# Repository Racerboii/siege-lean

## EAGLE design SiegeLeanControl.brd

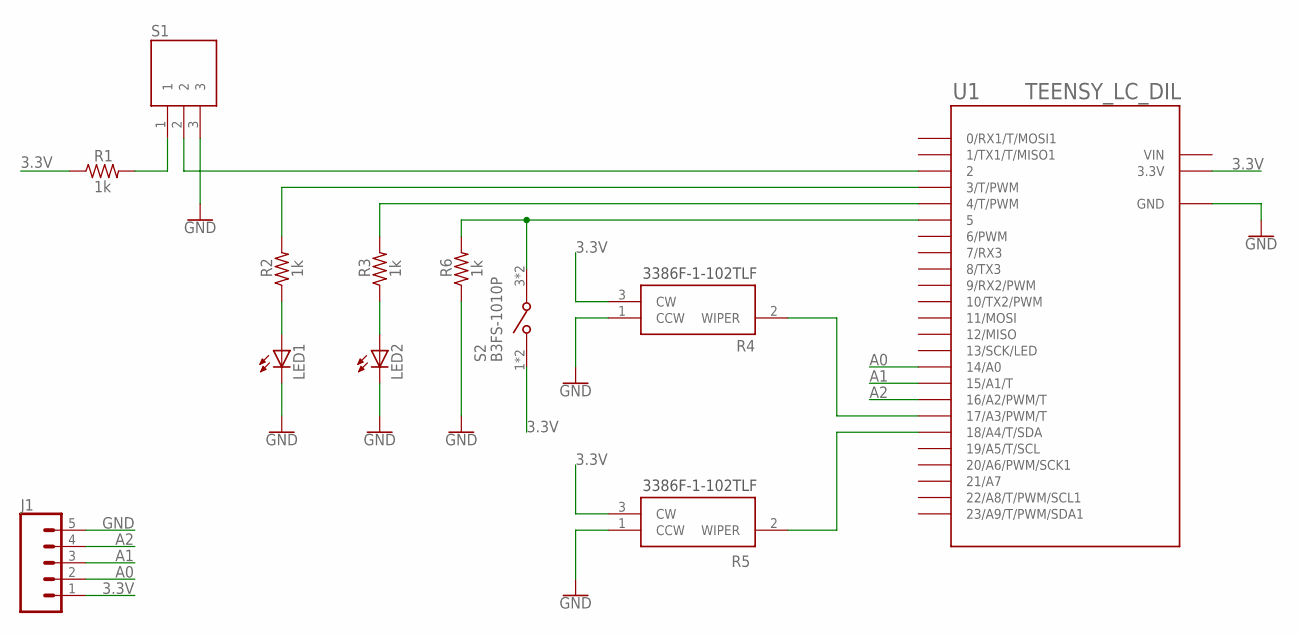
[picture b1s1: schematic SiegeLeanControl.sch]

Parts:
J1: CONN_05; 1X05
LED1, LED2: LEDCHIPLED_1206; CHIPLED_1206
R1, R2, R3, R6: 1k; R1206
R4, R5: 3386F-1-103TLF; 3386F1103TLF
S1: OS102011MA1QN1
S2: B3FS-1010P; SW_B3FS-1010P
U1: TEENSY_LC_DIL; TEENSY_3.0-3.2&LC_DIL

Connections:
3.3V: J1.1, R1.1, R4.3 (CW), R5.3 (CW), S2.1, S2.2 (1), U1.3.3V
A0: J1.2, U1.14/A0
A1: J1.3, U1.15/A1 (15/A1/T)
A2: J1.4, U1.16/A2 (16/A2/PWM/T)
GND: J1.5, LED1.C, LED2.C, R4.1 (CCW), R5.1 (CCW), R6.1, S1.3, U1.AGND (GND), U1.GND
unnamed: S1.2, U1.2
unnamed: R1.2, S1.1
unnamed: R2.2, U1.3 (3/T/PWM)
unnamed: R3.2, U1.4 (4/T/PWM)
unnamed: LED1.A, R2.1
unnamed: LED2.A, R3.1
unnamed: R4.2 (WIPER), U1.17/A3 (17/A3/PWM/T)
unnamed: R6.2, S2.3 (2), S2.4 (2), U1.5
unnamed: R5.2 (WIPER), U1.18/A4 (18/A4/T/SDA)
VIN: U1.VIN

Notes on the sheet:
3386F-1-102TLF

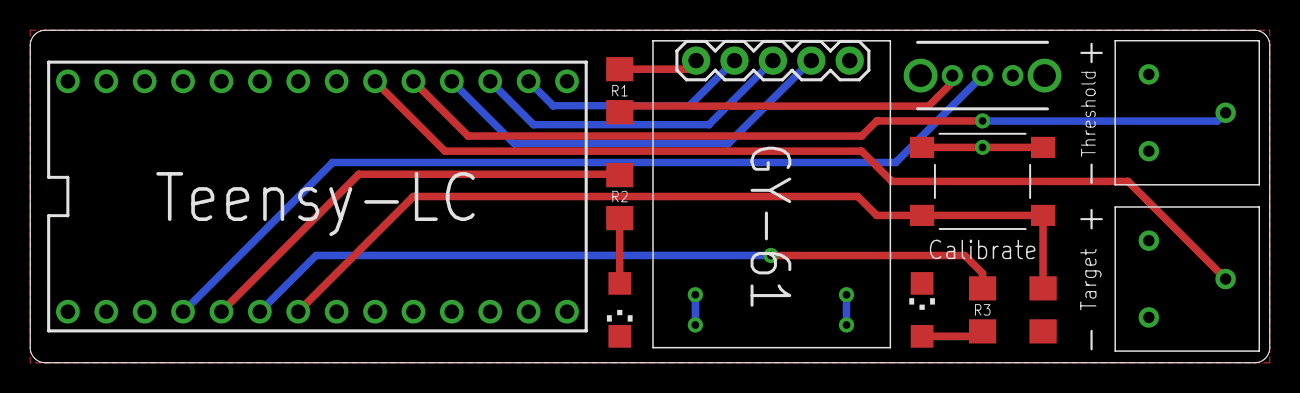
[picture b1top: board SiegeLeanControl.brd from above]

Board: 2 copper layers, 82.0 x 22.0 mm, 12 parts (0 on the bottom side), 14 nets.

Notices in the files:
parts and their libraries:
SparkFun-Connectors: Licensing: Creative Commons ShareAlike 4.0 International - https://creativecommons.org/licenses/by-sa/4.0
